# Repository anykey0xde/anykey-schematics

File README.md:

NOTICE
======

This repository has moved.

Please find it here [https://github.com/presseverykey/everykey-schematics](https://github.com/presseverykey/everykey-schematics)

Just a quick notice to anyone potentially tracking these repositories: we've been informed that 
we are causing some confusion with an IT-system house named anykey GmbH.

In case you are looking for a company in Sankt Augustin, Germany
providing Oracle, EMC, or similar data center solutions, we apologize
for any inconvenience or confusion we may have caused. You want to be
[here](http://www.anykey.de/).

If you're looking for the Open Source ARM Cortex M3 embedded development
board, we've moved all our Open Source efforts to a new github account: [presseverykey](https://github.com/presseverykey).

Thanks and again, apologies for any confusion.

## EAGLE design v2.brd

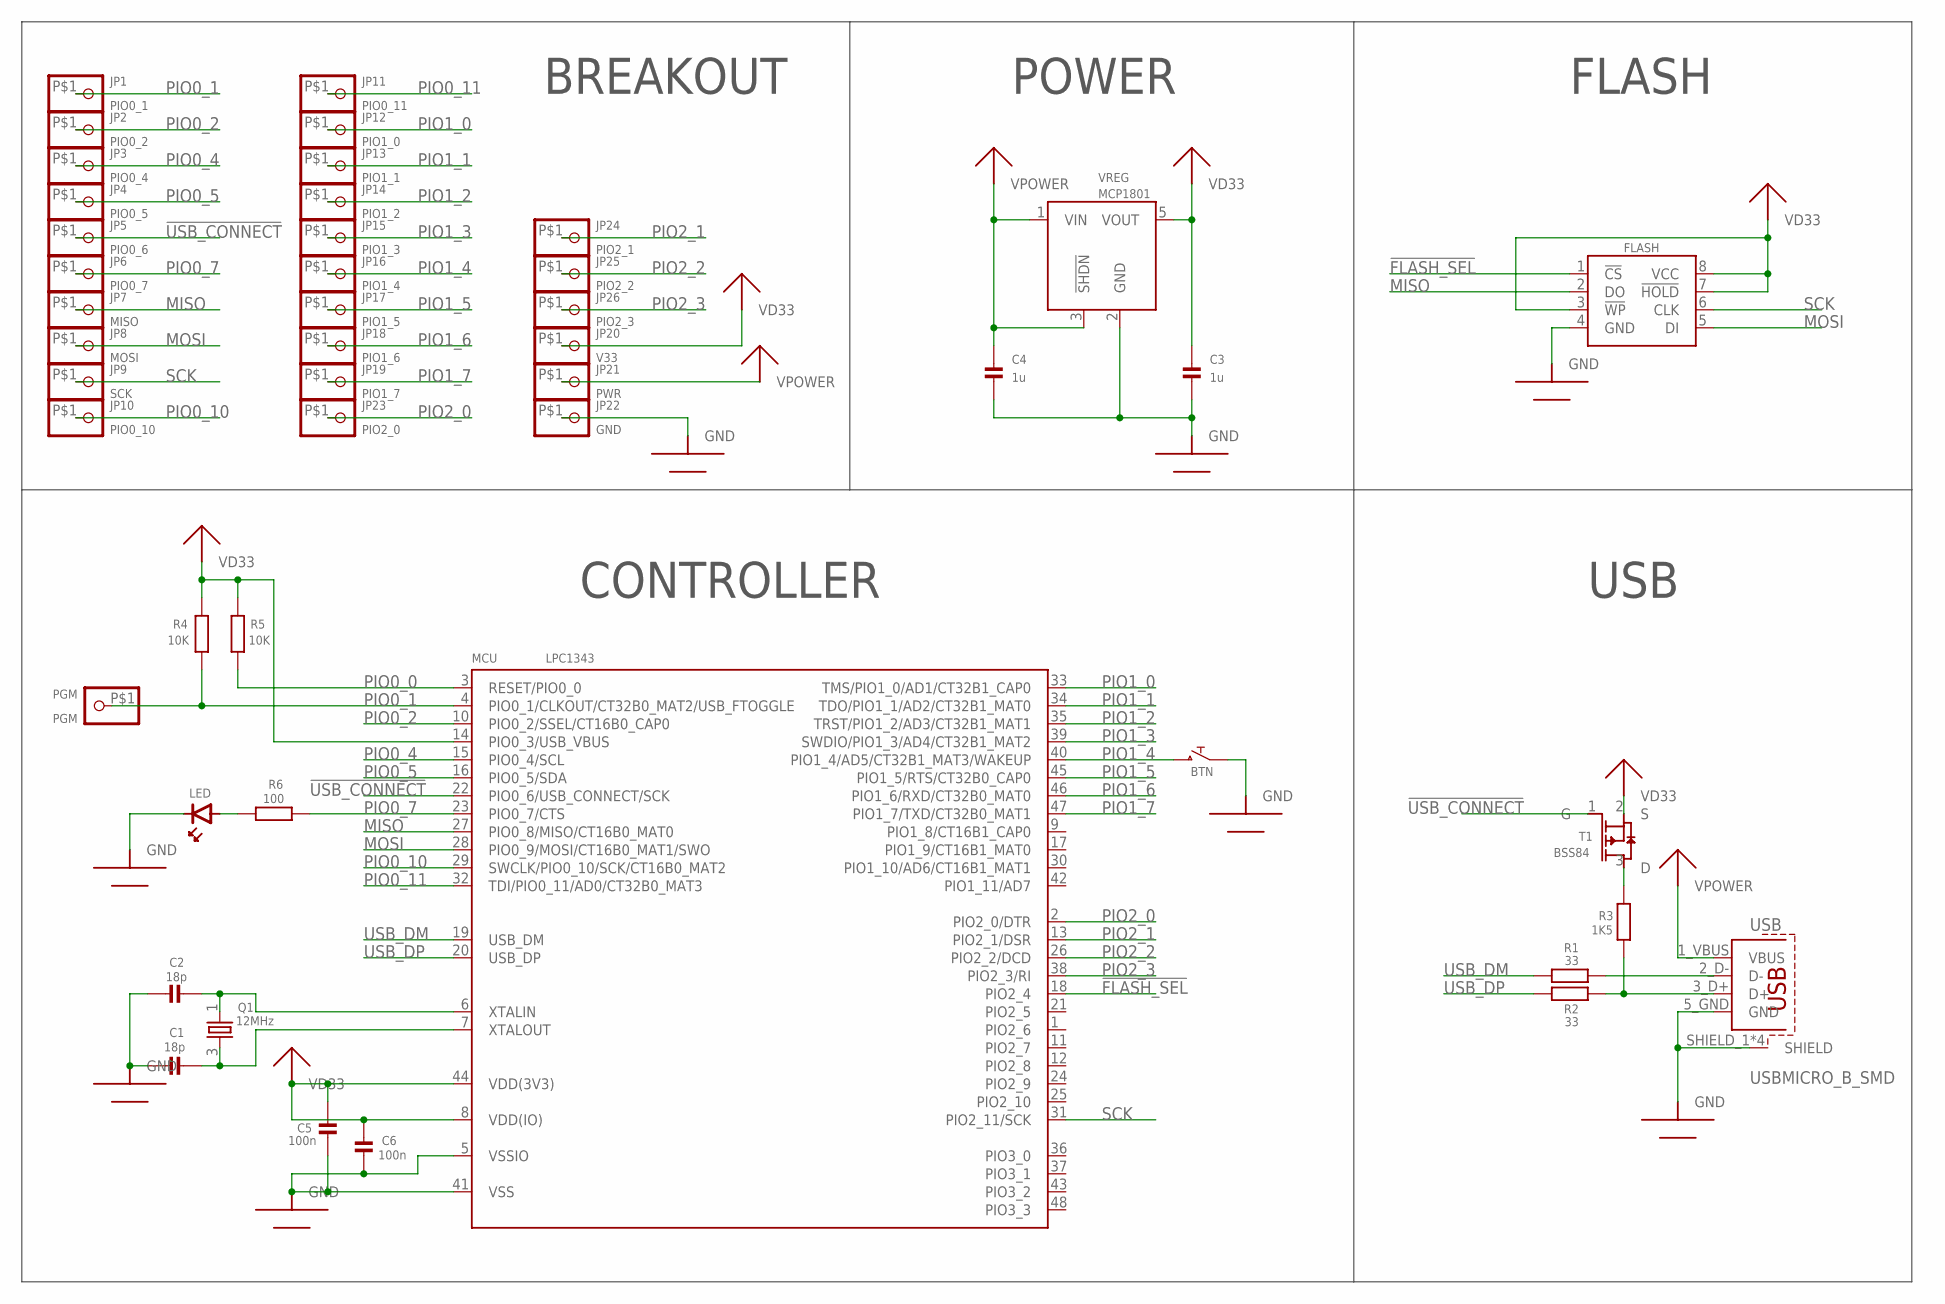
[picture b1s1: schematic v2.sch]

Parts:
BTN: PUSHBUTTONEVQP0; EVQP0
C1, C2: 18p; 0805_MICROMELF_COMBO
C3, C4: 1u; 0805_MICROMELF_COMBO
C5, C6: 100n; 0805_MICROMELF_COMBO
FLASH: SERIALFLASHSOIC8-150MIL; SOIC8-150MIL
JP1: PIO0_1; PCB_MEDIUM_RECT_PAD
JP2: PIO0_2; PCB_MEDIUM_RECT_PAD
JP3: PIO0_4; PCB_MEDIUM_RECT_PAD
JP4: PIO0_5; PCB_MEDIUM_RECT_PAD
JP5: PIO0_6; PCB_MEDIUM_RECT_PAD
JP6: PIO0_7; PCB_MEDIUM_RECT_PAD
JP7: MISO; PCB_MEDIUM_RECT_PAD
JP8: MOSI; PCB_MEDIUM_RECT_PAD
JP9: SCK; PCB_MEDIUM_RECT_PAD
JP10: PIO0_10; PCB_MEDIUM_RECT_PAD
JP11: PIO0_11; PCB_MEDIUM_RECT_PAD
JP12: PIO1_0; PCB_MEDIUM_RECT_PAD
JP13: PIO1_1; PCB_MEDIUM_RECT_PAD
JP14: PIO1_2; PCB_MEDIUM_RECT_PAD
JP15: PIO1_3; PCB_MEDIUM_RECT_PAD
JP16: PIO1_4; PCB_MEDIUM_RECT_PAD
JP17: PIO1_5; PCB_MEDIUM_RECT_PAD
JP18: PIO1_6; PCB_MEDIUM_RECT_PAD
JP19: PIO1_7; PCB_MEDIUM_RECT_PAD
JP20: V33; PCB_MEDIUM_RECT_PAD
JP21: PWR; PCB_MEDIUM_RECT_PAD
JP22: GND; PCB_MEDIUM_RECT_PAD
JP23: PIO2_0; PCB_MEDIUM_RECT_PAD
JP24: PIO2_1; PCB_MEDIUM_RECT_PAD
JP25: PIO2_2; PCB_MEDIUM_RECT_PAD
JP26: PIO2_3; PCB_MEDIUM_RECT_PAD
LED: 0805_POLAR
MCU: LPC1343; LQFP48
PGM: PGM; PCB_MEDIUM_RECT_PAD
Q1: 12MHz; ABM8G
R1, R2: 33; 0805_MICROMELF_COMBO
R3: 1K5; 0805_MICROMELF_COMBO
R4, R5: 10K; 0805_MICROMELF_COMBO
R6: 100; 0805_MICROMELF_COMBO
T1: BSS84; SOT23
USB: USBMICRO_B_SMD; MICRO_USB_B_SMD
VREG: MCP1801; SOT-23-5

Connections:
!FLASH_SEL: FLASH.1 (!CS), MCU.18 (PIO2_4)
!USB_CONNECT: JP5.P$1, MCU.22 (PIO0_6/USB_CONNECT/SCK), T1.1 (G)
GND: BTN.A (1), C1.1, C2.1, C3.2, C4.2, C5.2, C6.2, FLASH.4 (GND), JP22.P$1, LED.K (CATHODE), MCU.5 (VSSIO), MCU.41 (VSS), USB.5_GND (GND), USB.SHIELD_1 (SHIELD), USB.SHIELD_2 (SHIELD), USB.SHIELD_3 (SHIELD), USB.SHIELD_4 (SHIELD), VREG.2 (GND)
MISO: FLASH.2 (DO), JP7.P$1, MCU.27 (PIO0_8/MISO/CT16B0_MAT0)
MOSI: FLASH.5 (DI), JP8.P$1, MCU.28 (PIO0_9/MOSI/CT16B0_MAT1/SWO)
unnamed: C2.2, MCU.6 (XTALIN), Q1.1
unnamed: C1.2, MCU.7 (XTALOUT), Q1.3 (2)
unnamed: R3.1, T1.3 (D)
unnamed: R1.1, USB.2_D- (D-)
unnamed: LED.A (ANODE), R6.1
PIO0_0: MCU.3 (RESET/PIO0_0), R5.1
PIO0_1: JP1.P$1, MCU.4 (PIO0_1/CLKOUT/CT32B0_MAT2/USB_FTOGGLE), PGM.P$1, R4.1
PIO0_2: JP2.P$1, MCU.10 (PIO0_2/SSEL/CT16B0_CAP0)
PIO0_4: JP3.P$1, MCU.15 (PIO0_4/SCL)
PIO0_5: JP4.P$1, MCU.16 (PIO0_5/SDA)
PIO0_7: JP6.P$1, MCU.23 (PIO0_7/CTS), R6.2
PIO0_10: JP10.P$1, MCU.29 (SWCLK/PIO0_10/SCK/CT16B0_MAT2)
PIO0_11: JP11.P$1, MCU.32 (TDI/PIO0_11/AD0/CT32B0_MAT3)
PIO1_0: JP12.P$1, MCU.33 (TMS/PIO1_0/AD1/CT32B1_CAP0)
PIO1_1: JP13.P$1, MCU.34 (TDO/PIO1_1/AD2/CT32B1_MAT0)
PIO1_2: JP14.P$1, MCU.35 (TRST/PIO1_2/AD3/CT32B1_MAT1)
PIO1_3: JP15.P$1, MCU.39 (SWDIO/PIO1_3/AD4/CT32B1_MAT2)
PIO1_4: BTN.B (2), JP16.P$1, MCU.40 (PIO1_4/AD5/CT32B1_MAT3/WAKEUP)
PIO1_5: JP17.P$1, MCU.45 (PIO1_5/RTS/CT32B0_CAP0)
PIO1_6: JP18.P$1, MCU.46 (PIO1_6/RXD/CT32B0_MAT0)
PIO1_7: JP19.P$1, MCU.47 (PIO1_7/TXD/CT32B0_MAT1)
PIO2_0: JP23.P$1, MCU.2 (PIO2_0/DTR)
PIO2_1: JP24.P$1, MCU.13 (PIO2_1/DSR)
PIO2_2: JP25.P$1, MCU.26 (PIO2_2/DCD)
PIO2_3: JP26.P$1, MCU.38 (PIO2_3/RI)
SCK: FLASH.6 (CLK), JP9.P$1, MCU.31 (PIO2_11/SCK)
USB_D+: R2.1, R3.2, USB.3_D+ (D+)
USB_DM: MCU.19 (USB_DM), R1.2
USB_DP: MCU.20 (USB_DP), R2.2
VD33: C3.1, C5.1, C6.1, FLASH.3 (!WP), FLASH.7 (!HOLD), FLASH.8 (VCC), JP20.P$1, MCU.8 (VDD(IO)), MCU.14 (PIO0_3/USB_VBUS), MCU.44 (VDD(3V3)), R4.2, R5.2, T1.2 (S), VREG.5 (VOUT)
VPOWER: C4.1, JP21.P$1, USB.1_VBUS (VBUS), VREG.1 (VIN), VREG.3 (!SHDN)

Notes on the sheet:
FLASH
POWER
USB
BREAKOUT
CONTROLLER

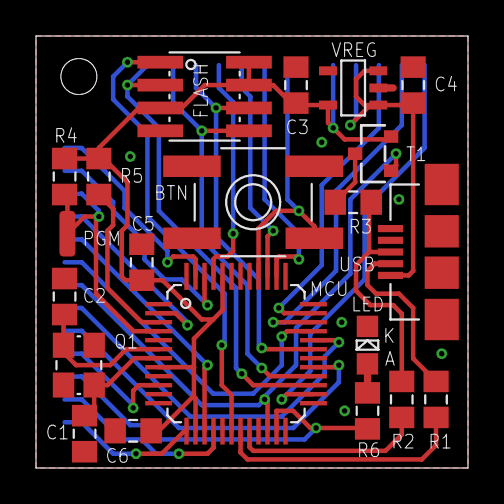
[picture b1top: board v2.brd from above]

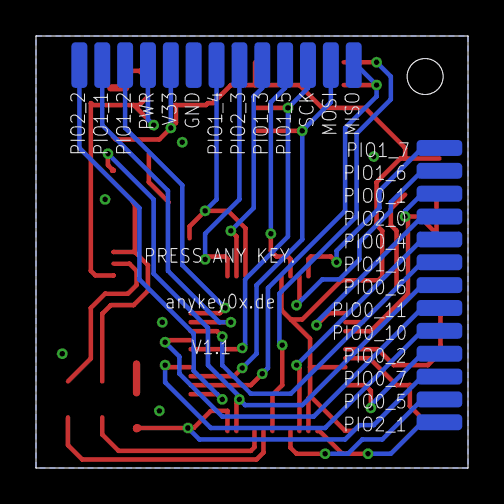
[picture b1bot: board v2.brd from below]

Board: 2 copper layers, 24.0 x 24.0 mm, 47 parts (26 on the bottom side), 36 nets.

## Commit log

2012-03-18 initial
2012-03-18 changed voltage regulator, routed more pins
2012-03-18 vreg label 1801
2012-03-19 moved via
2012-03-19 Added drill hole, simplified routing, added version number on silkscreen, flash pinout fix, added softconnect transistor
2012-03-19 Added softconnect transistor, vast cleanup
2012-03-19 Fixed SOIC8 / Serialflash pinout
2012-03-20 Changed mounting hole to drill, adjustments to meet Makepcb.com design limitations (i.e. move oscillator), some more trace straightening
2012-03-20 Board adjustments to comply with MakePCB.com
2012-03-20 Gerber files for v1.0 PCB order
2012-03-23 Added button outline (to get a better impression of space inside the device)
2012-05-13 Lessons learned: Larger font, reversed USB Pullup, clearer silkscreen, wider and rounded solder pads
2012-08-15 pdf and png version of schematics
2014-04-13 rename
2014-04-13 update notice
2014-04-13 updated notice
2014-04-13 phrasing
